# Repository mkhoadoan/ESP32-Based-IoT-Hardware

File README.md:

# ESP32-Based-IoT-Hardware
Design of IoT hardware base on ESP-32 Microcontroller using KiCAD 9.0

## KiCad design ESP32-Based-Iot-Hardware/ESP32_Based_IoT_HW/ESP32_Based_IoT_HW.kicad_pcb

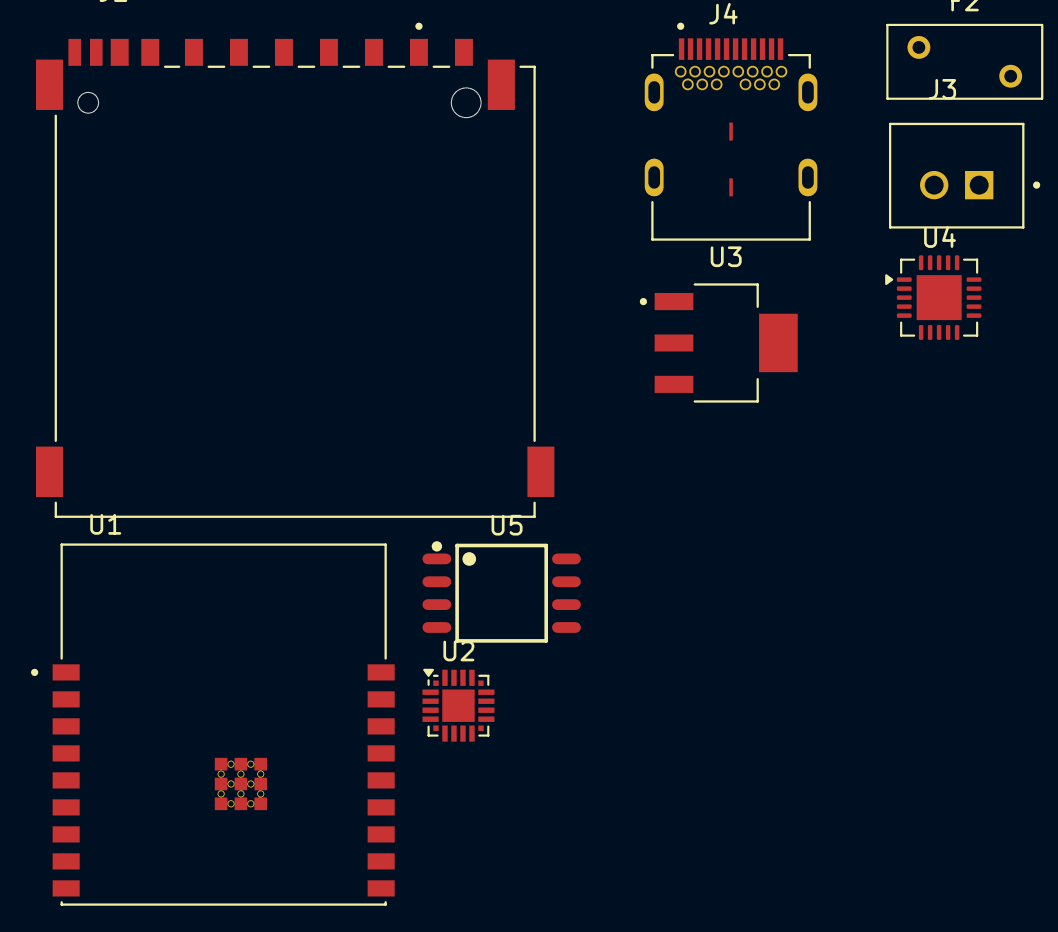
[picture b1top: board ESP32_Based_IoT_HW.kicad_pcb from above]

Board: 2 copper layers, 9 parts (0 on the bottom side), 9 nets, no tracks yet.

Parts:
F2: Fuse; Fuse_BelFuse_0ZRE0005FF_L8.3mm_W3.8mm
J1: GSD090012SEU; AMPHENOL_GSD090012SEU
J3: JST_2Pin_Connector; JST_B2B-XH-A__LF__SN_
J4: SS-52400-002; BELFUSE_SS-52400-002
U1: ESP32-C3-WROOM-02-H4; MODULE_ESP32-C3-WROOM-02-H4
U2: CP2102N-Axx-xQFN20; SiliconLabs_QFN-20-1EP_3x3mm_P0.5mm_EP1.8x1.8mm
U3: LM1117MPX-3.3_NOPB; VREG_LM1117MPX-3.3_NOPB
U4: MCP73871; QFN-20-1EP_4x4mm_P0.5mm_EP2.5x2.5mm
U5: W25Q32JVSSIQ; SOIC127P790X216-8N

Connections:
+5V: U3.3 (VIN), U4.1 (OUT), U4.20 (OUT)
+BATT: J3.2, U4.14 (V_{BAT}), U4.15 (V_{BAT}), U4.16 (V_{BAT_SENSE})
/+5V_USB: F2.2, U4.2 (VPCC), U4.3 (SEL), U4.4 (PROG2), U4.17 (CE), U4.18 (IN), U4.19 (IN)
/USB_DN: J4.A7 (DN1), J4.B7 (DN2)
/USB_DP: J4.A6 (DP1), J4.B6 (DP2)
/VBUS: F2.1, J4.A4 (VBUSA1), J4.A9 (VBUSA2), J4.B4 (VBUSB1), J4.B9 (VBUSB2)
GND: J3.1, J4.A1 (GNDA1), J4.A12 (GNDA2), J4.B1 (GNDB1), J4.B12 (GNDB2), J4.G1 (GND/SHIELD), J4.G2 (GND/SHIELD), J4.G3 (GND/SHIELD), J4.G4 (GND/SHIELD), J4.S1 (GND/SHIELD), J4.S2 (GND/SHIELD), J4.S3 (GND/SHIELD), J4.S4 (GND/SHIELD), U1.9 (GND), U1.19 (GND), U1.20 (GND), U1.21 (GND), U1.22 (GND), U1.23 (GND), U1.24 (GND), U1.25 (GND), U1.26 (GND), U1.27 (GND), U1.28 (GND), U1.29 (GND), U1.30 (GND), U1.31 (GND), U1.32 (GND), U1.33 (GND), U1.34 (GND), U1.35 (GND), U1.36 (GND), U1.37 (GND), U1.38 (GND), U1.39 (GND), U3.1 (GND), U4.10 (V_{SS}), U4.11 (V_{SS}), U4.21 (V_{SS})
unnamed: U2.3 (GND), U2.12 (GND), U2.21 (GND)
SHIELD_GND: J1.G1 (SHIELD_GND), J1.G2 (SHIELD_GND), J1.G3 (SHIELD_GND), J1.G4 (SHIELD_GND)

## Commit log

2025-11-05 Add files via upload
    First version
